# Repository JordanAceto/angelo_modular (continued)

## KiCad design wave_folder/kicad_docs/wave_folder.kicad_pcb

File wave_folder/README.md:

# Wavefolder

The wavefolder is a unique waveshaping circuit that creates "folded" versions of sloping input waveforms.

CV inputs for folds, shape, and offset are included.

A bonus ring-modulator circuit is included, to maintain compatability with the old module.

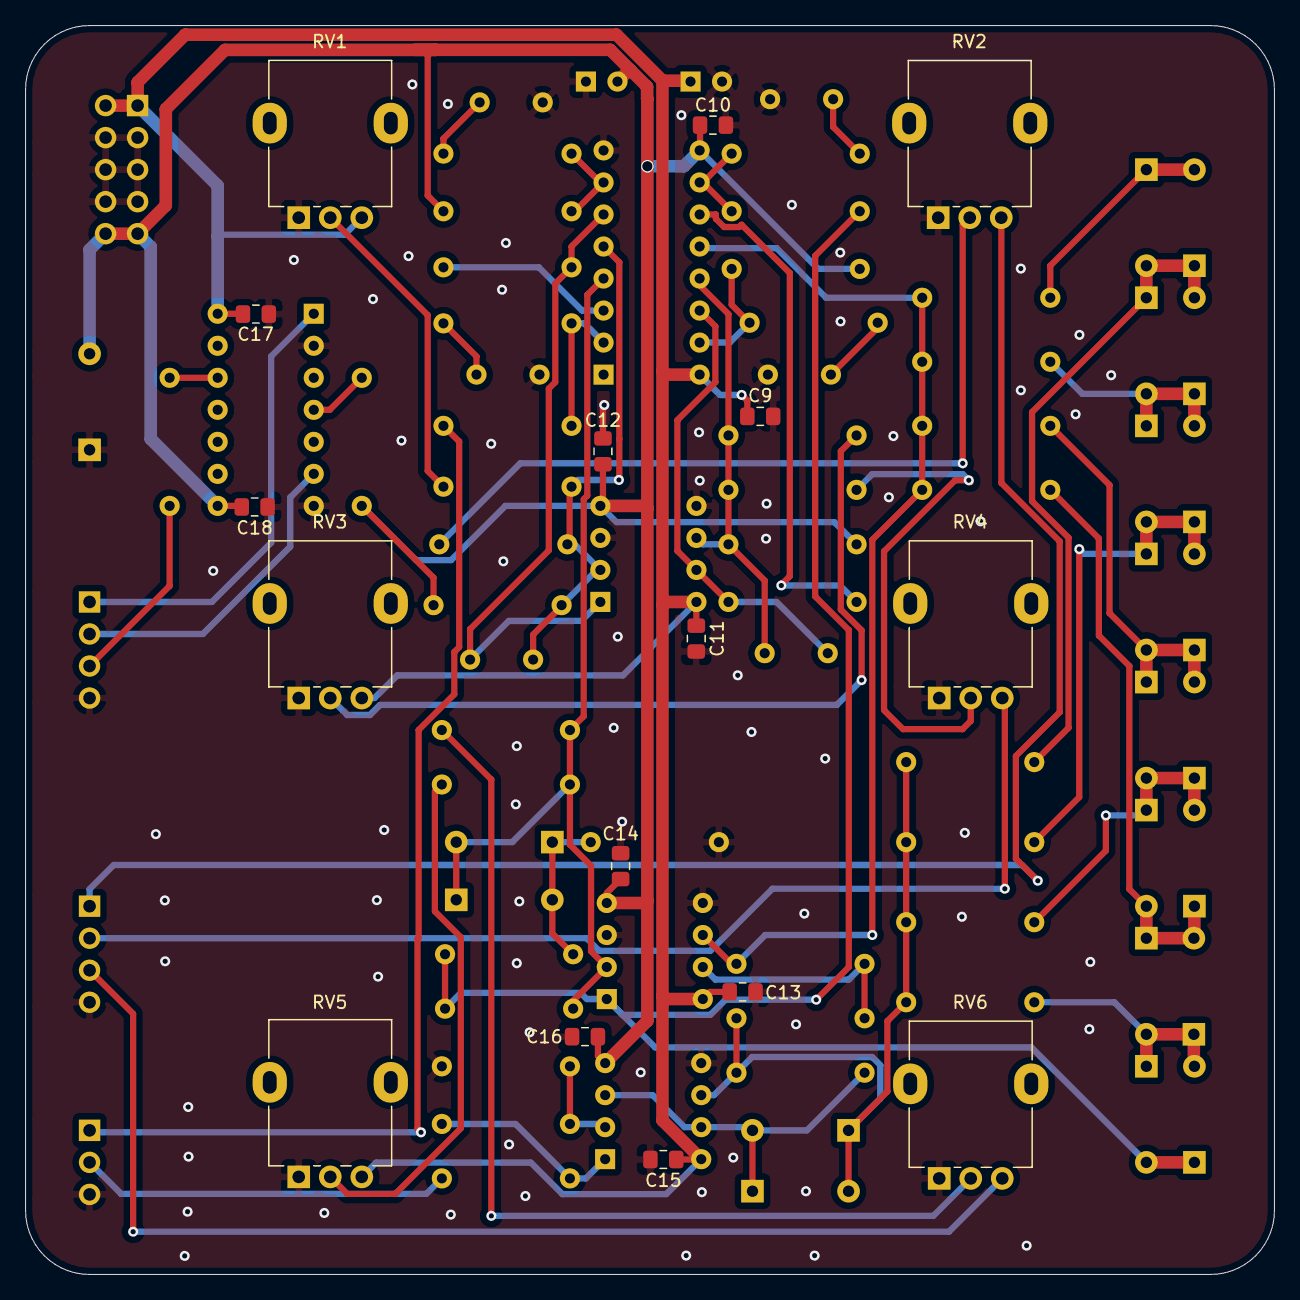
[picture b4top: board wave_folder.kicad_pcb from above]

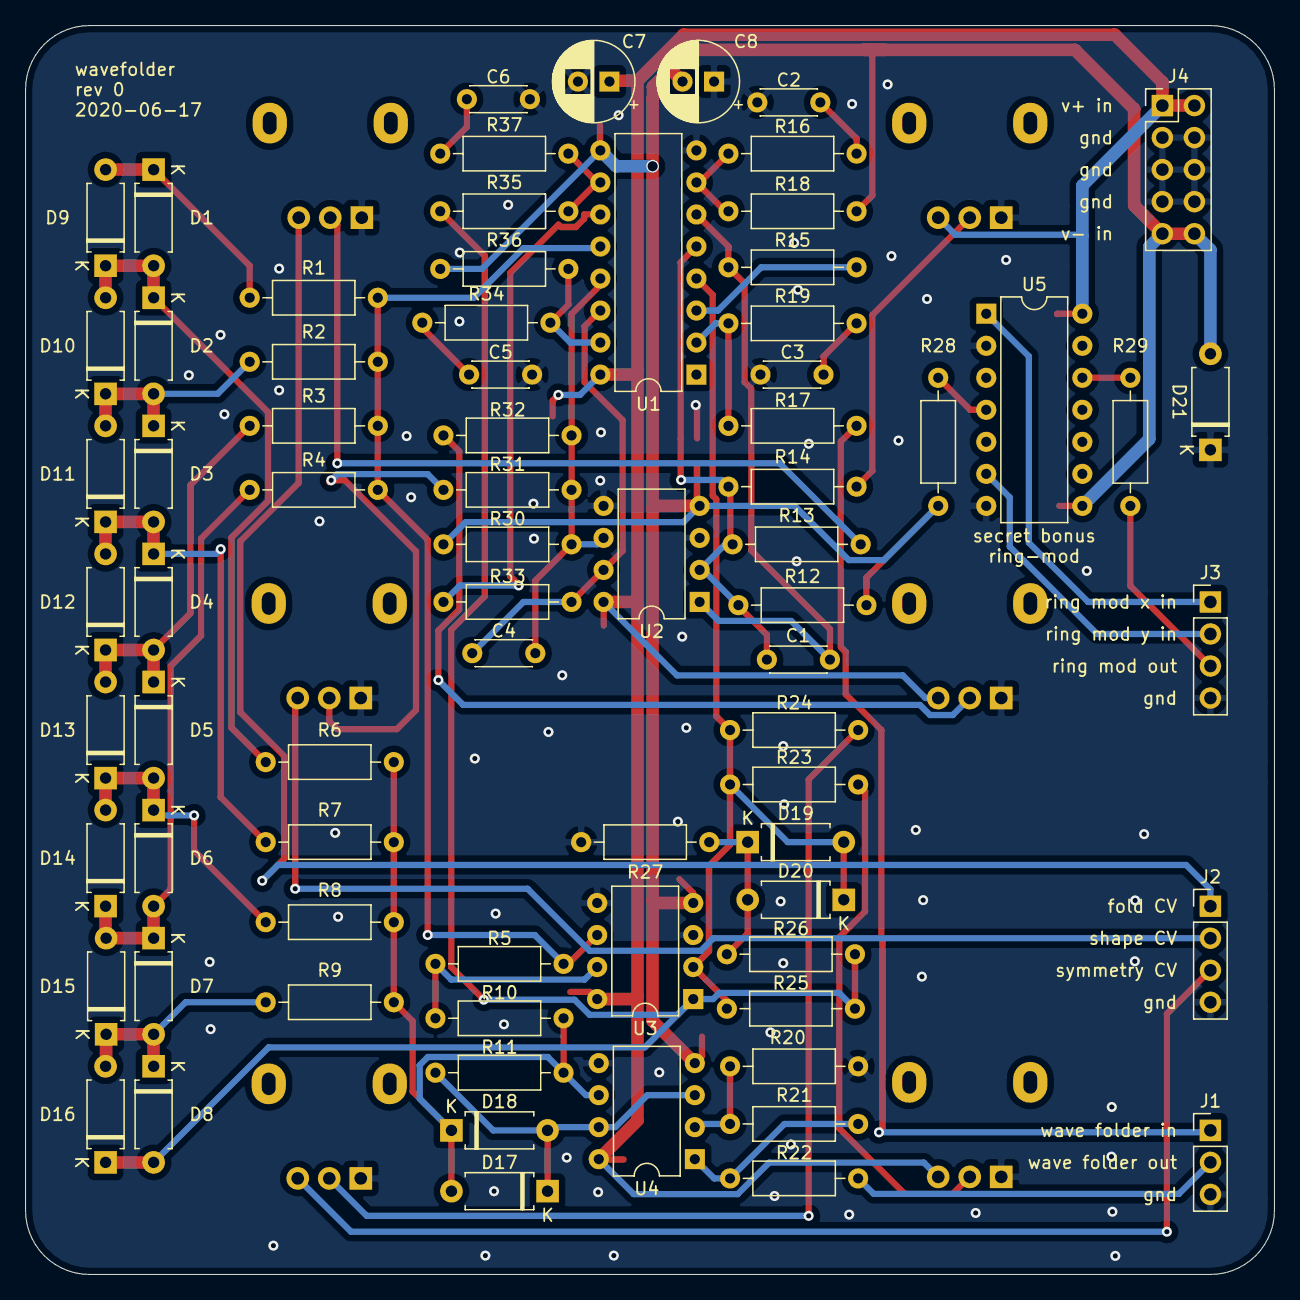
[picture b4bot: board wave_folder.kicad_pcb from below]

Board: 2 copper layers, 99.1 x 99.1 mm, 91 parts (75 on the bottom side), 50 nets.

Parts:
C1, C4: 100pF; C_Disc_D4.3mm_W1.9mm_P5.00mm
C2, C3, C5, C6: 560pF; C_Disc_D4.3mm_W1.9mm_P5.00mm
C7, C8: 10uF; CP_Radial_D6.3mm_P2.50mm
C9, C10, C11, C12, C13, C14, C15, C16, C17, C18: 100nF; C_0805_2012Metric_Pad1.15x1.40mm_HandSolder
D1, D2, D3, D4, D5, D6, D7, D8, D9, D10, D11, D12, D13, D14, D15, D16, D17, D18, D19, D20: D; D_A-405_P7.62mm_Horizontal
D21: D_Schottky; D_A-405_P7.62mm_Horizontal
J1: signal_port; PinHeader_1x03_P2.54mm_Vertical
J2: CV_port; PinHeader_1x04_P2.54mm_Vertical
J3: ring_mod_port; PinHeader_1x04_P2.54mm_Vertical
J4: power_in_connector; PinHeader_2x05_P2.54mm_Vertical
R1, R2, R3, R4, R6, R7, R8, R9: 15k; R_Axial_DIN0207_L6.3mm_D2.5mm_P10.16mm_Horizontal
R5, R10, R28: 5k6; R_Axial_DIN0207_L6.3mm_D2.5mm_P10.16mm_Horizontal
R11: 56k; R_Axial_DIN0207_L6.3mm_D2.5mm_P10.16mm_Horizontal
R12: dnf; R_Axial_DIN0207_L6.3mm_D2.5mm_P10.16mm_Horizontal
R13, R17, R24, R31: 100k; R_Axial_DIN0207_L6.3mm_D2.5mm_P10.16mm_Horizontal
R14, R23, R32: 220k; R_Axial_DIN0207_L6.3mm_D2.5mm_P10.16mm_Horizontal
R15, R33: 4k7; R_Axial_DIN0207_L6.3mm_D2.5mm_P10.16mm_Horizontal
R16, R19, R34, R37: 510; R_Axial_DIN0207_L6.3mm_D2.5mm_P10.16mm_Horizontal
R18, R36: 240k; R_Axial_DIN0207_L6.3mm_D2.5mm_P10.16mm_Horizontal
R20: 7k5; R_Axial_DIN0207_L6.3mm_D2.5mm_P10.16mm_Horizontal
R21: 82k; R_Axial_DIN0207_L6.3mm_D2.5mm_P10.16mm_Horizontal
R22, R29: 1k; R_Axial_DIN0207_L6.3mm_D2.5mm_P10.16mm_Horizontal
R25: 180k; R_Axial_DIN0207_L6.3mm_D2.5mm_P10.16mm_Horizontal
R26: 33k; R_Axial_DIN0207_L6.3mm_D2.5mm_P10.16mm_Horizontal
R27: 2k7; R_Axial_DIN0207_L6.3mm_D2.5mm_P10.16mm_Horizontal
R30: 10M; R_Axial_DIN0207_L6.3mm_D2.5mm_P10.16mm_Horizontal
R35: 27k; R_Axial_DIN0207_L6.3mm_D2.5mm_P10.16mm_Horizontal
RV1, RV2, RV3, RV4, RV5, RV6: 100k; Potentiometer_Alpha_RD901F-40-00D_Single_Vertical
U1: SSM2164; DIP-16_W7.62mm
U2, U3, U4: TL072; DIP-8_W7.62mm
U5: AD534; DIP-14_W7.62mm

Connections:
+12V: C7.1, C9.1, C11.1, C13.1, C15.1, C17.1, J4.1, J4.2, RV1.3, RV3.3, RV5.3, U1.16, U2.8, U3.8, U4.8, U5.14
-12V: C8.2, C10.2, C12.2, C14.2, C16.2, C18.2, D21.2, J4.9, J4.10, R12.2, R18.1, R28.2, R30.2, R36.1, U1.9, U2.4, U3.4, U4.4, U5.8
/core/core_i_in: R1.2, R2.2, R3.2, R4.2, R5.2, U1.12, U3.6
/core/core_out: D17.1, D18.2, R11.1, U4.3, U4.7
/core/core_v_in: D8.2, D16.1, R25.1, R26.1, R35.2, U3.1
/folds_CV: R13.2, RV2.2
/folds_CV_in: J2.1, RV2.3
/folds_VCA/folds_VCA_signal_i_out: D19.2, D20.1, R23.1, R24.1, R25.2, U1.4, U3.2
/manual_folds: R14.2, RV1.2
/manual_shape: R32.2, RV3.2
/manual_symmetry: R23.2, RV5.2
/ring_mod_out: J3.3, R29.1
/ring_mod_x_in: J3.1, U5.1
/ring_mod_y_in: J3.2, U5.6
/shape_CV: R31.2, RV4.2
/shape_CV_in: J2.2, RV4.3
/signal_in: J1.1, R17.2
/signal_out: J1.2, R22.2
/symmetry_CV: R24.2, RV6.2
/symmetry_CV_in: J2.3, RV6.3
GND: C2.2, C3.2, C5.2, C6.2, C7.2, C8.1, C9.2, C10.1, C11.2, C12.1, C13.2, C14.1, C15.2, C16.1, C17.2, C18.1, D21.1, J1.3, J2.4, J3.4, J4.3, J4.4, J4.5, J4.6, J4.7, J4.8, R20.1, R27.2, RV1.1, RV2.1, RV3.1, RV4.1, RV5.1, RV6.1, U1.8, U2.3, U2.5, U3.3, U3.5, U4.5, U5.2, U5.7
unnamed: C1.1, R15.2, U1.6, U2.1
unnamed: C1.2, R12.1, R13.1, R14.1, U1.5, U2.2
unnamed: C2.1, R16.1
unnamed: C3.1, R19.1
unnamed: C4.1, R33.2, U1.14, U2.7
unnamed: C4.2, R30.1, R31.1, R32.1, U1.13, U2.6
unnamed: C5.1, R34.1
unnamed: C6.1, R37.1
unnamed: D1.1, D9.2, R1.1
unnamed: D1.2, D2.1, D9.1, D10.2, R6.2
unnamed: D2.2, D3.1, D10.1, D11.2, R2.1
unnamed: D3.2, D4.1, D11.1, D12.2, R7.2
unnamed: D4.2, D5.1, D12.1, D13.2, R3.1
unnamed: D5.2, D6.1, D13.1, D14.2, R8.2
unnamed: D6.2, D7.1, D14.1, D15.2, R4.1
unnamed: D7.2, D8.1, D15.1, D16.2, R9.2
unnamed: D17.2, D18.1, R6.1, R7.1, R8.1, R9.1, R10.1, R11.2, U4.6
unnamed: D19.1, D20.2, R26.2, R27.1
unnamed: R5.1, R10.2, U3.7
unnamed: R15.1, U1.3
unnamed: R16.2, R18.2, U1.7
unnamed: R17.1, R19.2, U1.2
unnamed: R20.2, R21.1, U4.2
unnamed: R21.2, R22.1, U4.1
unnamed: R28.1, U5.4
unnamed: R29.2, U5.12
unnamed: R33.1, U1.11
unnamed: R34.2, R36.2, U1.15
unnamed: R35.1, R37.2, U1.10

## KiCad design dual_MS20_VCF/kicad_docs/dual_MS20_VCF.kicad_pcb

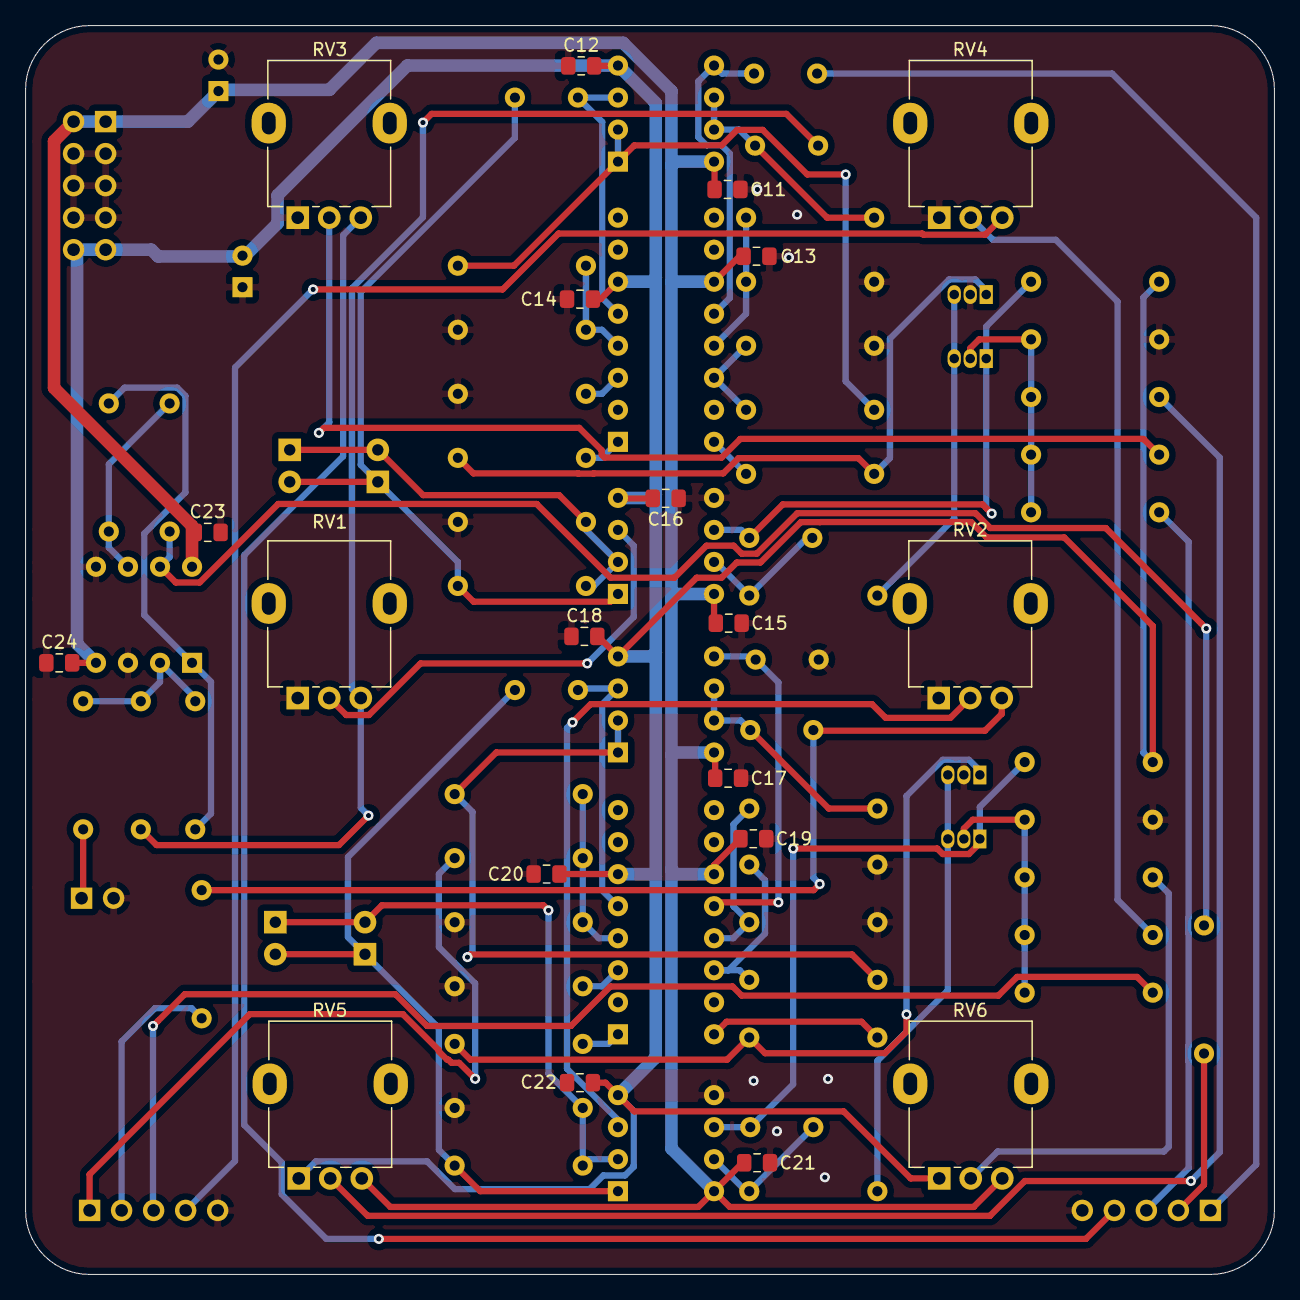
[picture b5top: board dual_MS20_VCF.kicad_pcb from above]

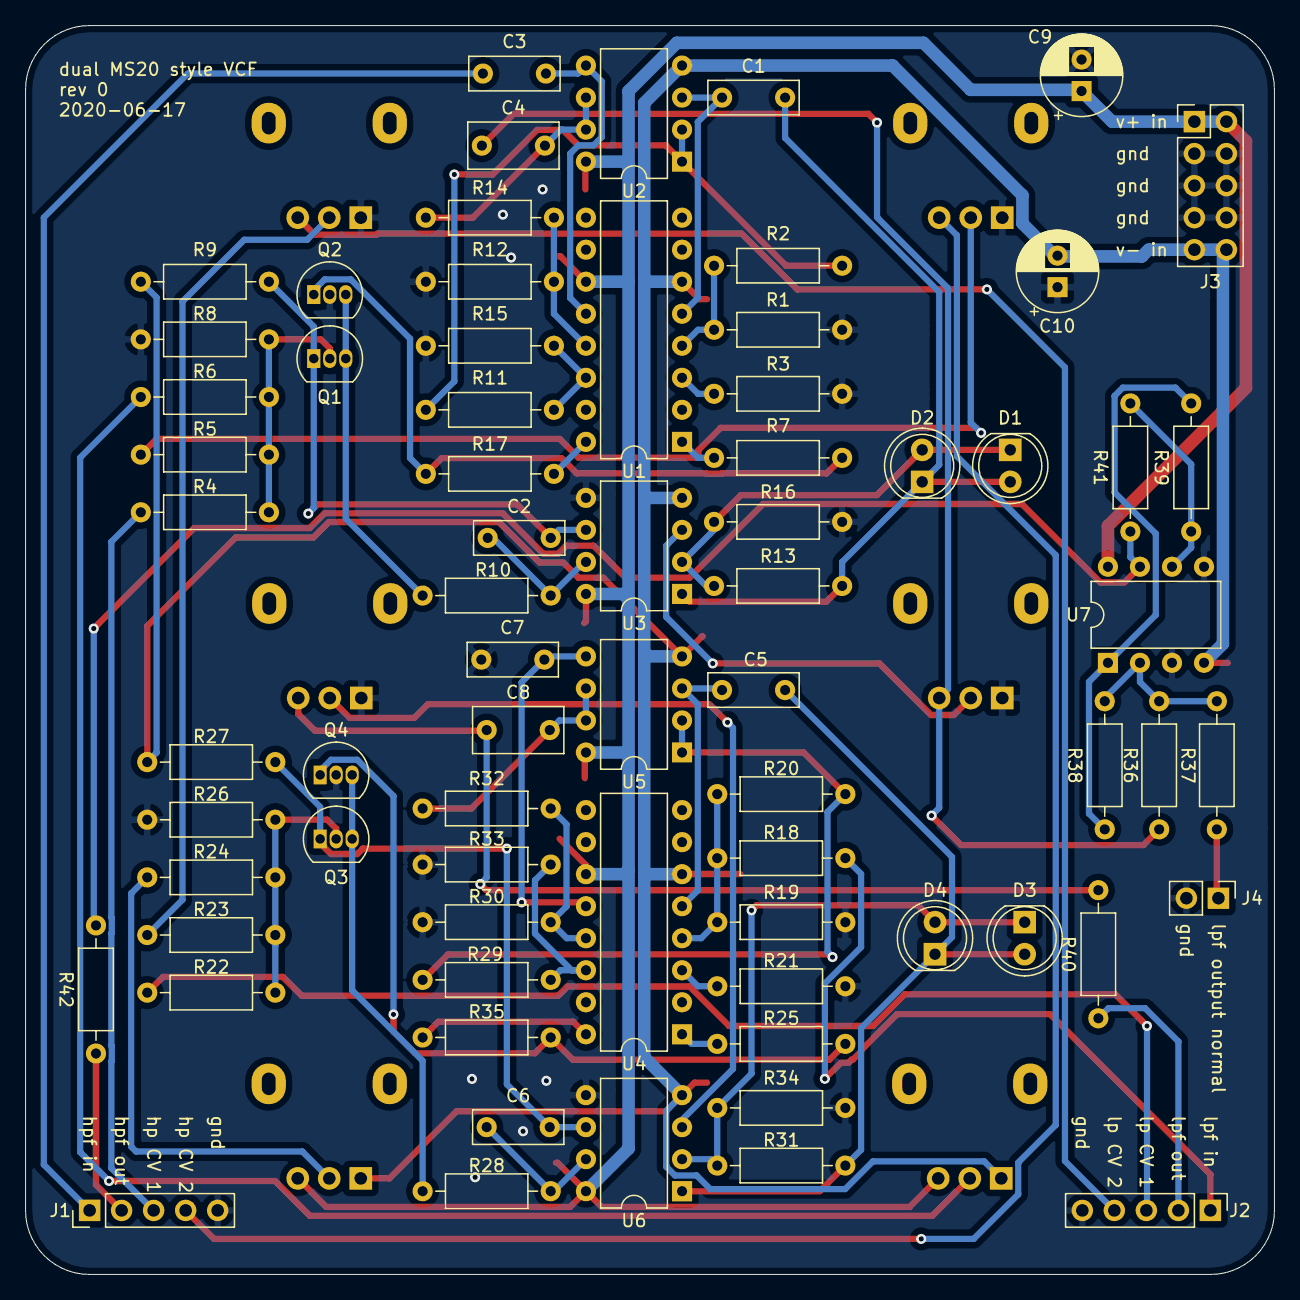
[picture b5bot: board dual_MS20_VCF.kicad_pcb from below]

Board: 2 copper layers, 99.1 x 99.1 mm, 91 parts (71 on the bottom side), 58 nets.

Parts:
C1, C3, C5, C7: 1nF; C_Rect_L7.0mm_W2.5mm_P5.00mm
C2, C6: 4n7; C_Rect_L7.0mm_W2.5mm_P5.00mm
C4, C8: 470nF; C_Rect_L7.0mm_W3.5mm_P5.00mm
C9, C10: 10uF; CP_Radial_D6.3mm_P2.50mm
C11, C12, C13, C14, C15, C16, C17, C18, C19, C20, C21, C22, C23, C24: 100nF; C_0805_2012Metric_Pad1.15x1.40mm_HandSolder
D1, D2, D3, D4: green; LED_D5.0mm
J1, J2: Conn_01x05; PinHeader_1x05_P2.54mm_Vertical
J3: power_in; PinHeader_2x05_P2.54mm_Vertical
J4: lpf_output_normal; PinHeader_1x02_P2.54mm_Vertical
Q1, Q2, Q3, Q4: BC558; TO-92_Inline
R1, R3, R12, R15, R19, R21, R30, R33: 220; R_Axial_DIN0207_L6.3mm_D2.5mm_P10.16mm_Horizontal
R2, R7, R11, R13, R14, R17, R18, R20, R25, R29, R31, R32, R35: 10k; R_Axial_DIN0207_L6.3mm_D2.5mm_P10.16mm_Horizontal
R4, R5, R22, R23, R36, R37, R38, R39, R41: 100k; R_Axial_DIN0207_L6.3mm_D2.5mm_P10.16mm_Horizontal
R6, R24: 240k; R_Axial_DIN0207_L6.3mm_D2.5mm_P10.16mm_Horizontal
R8, R16, R26, R34: 1k8; R_Axial_DIN0207_L6.3mm_D2.5mm_P10.16mm_Horizontal
R9, R27: 470k; R_Axial_DIN0207_L6.3mm_D2.5mm_P10.16mm_Horizontal
R10, R28: 4k7; R_Axial_DIN0207_L6.3mm_D2.5mm_P10.16mm_Horizontal
R40, R42: 1k; R_Axial_DIN0207_L6.3mm_D2.5mm_P10.16mm_Horizontal
RV1, RV2, RV3, RV4, RV5, RV6: 100k; Potentiometer_Alpha_RD901F-40-00D_Single_Vertical
U1, U4: LM13700; DIP-16_W7.62mm
U2, U3, U5, U6: MC1458; DIP-8_W7.62mm
U7: TL072; DIP-8_W7.62mm

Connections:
+12V: C9.1, C11.1, C13.1, C15.1, C17.1, C19.1, C21.1, C23.1, J3.1, J3.2, RV5.3, RV6.3, U1.11, U2.8, U3.8, U4.11, U5.8, U6.8, U7.8
-12V: C10.2, C12.2, C14.2, C16.2, C18.2, C20.2, C22.2, C24.2, J3.9, J3.10, R9.2, R27.2, RV5.1, RV6.1, U1.6, U2.4, U3.4, U4.6, U5.4, U6.4, U7.4
/HPF/hpf_cv_in_1: J1.3, R4.2
/HPF/hpf_cv_in_2: R5.2, RV3.2
/HPF/hpf_cv_in_3: R6.2, RV5.2
/HPF/hpf_in: C3.2, J1.1
/HPF/i_out: Q2.1, R7.1, R17.1
/LPF/i_out: Q4.1, R25.1, R35.1
/LPF/lpf_cv_in_1: J2.3, R22.2
/LPF/lpf_cv_in_2: R23.2, RV4.2
/LPF/lpf_cv_in_3: R24.2, RV6.2
/LPF/lpf_in: J2.1, R18.2
/LPF/lpf_out: C8.1, R40.2, RV2.3
/high_pass: C4.1, R36.2, RV1.3
/low_pass: J2.2, R40.1
/summed_hp_lp: J1.2, R42.1
GND: C7.2, C9.2, C10.1, C11.2, C12.1, C13.2, C14.1, C15.2, C16.1, C17.2, C18.1, C19.2, C20.1, C21.2, C22.1, C23.2, C24.1, J1.5, J2.5, J3.3, J3.4, J3.5, J3.6, J3.7, J3.8, J4.2, Q2.2, Q4.2, R1.2, R3.2, R8.2, R12.2, R15.2, R16.2, R19.2, R21.2, R26.2, R30.2, R33.2, R34.2, RV1.1, RV2.1, RV3.1, RV4.1, U3.5, U6.5, U7.3, U7.5
unnamed: C1.1, U1.5, U2.3
unnamed: C1.2, D1.2, D2.1, R13.2, U3.1
unnamed: C2.1, R10.1, U3.7
unnamed: C2.2, Q1.1, R9.1, U3.6
unnamed: C3.1, U1.12, U2.5
unnamed: C4.2, R14.1, U2.6, U2.7
unnamed: C5.1, U4.5, U5.3
unnamed: C5.2, D3.2, D4.1, R31.2, U6.1
unnamed: C6.1, R28.1, U6.7
unnamed: C6.2, Q3.1, R27.1, U6.6
unnamed: C7.1, U4.12, U5.5
unnamed: C8.2, R32.1, U5.6, U5.7
unnamed: D1.1, D2.2, R13.1, R16.1, U3.2
unnamed: D3.1, D4.2, R31.1, R34.1, U6.2
unnamed: J1.4, RV3.3
unnamed: J2.4, RV4.3
unnamed: J4.1, R37.2
unnamed: Q1.2, R4.1, R5.1, R6.1, R8.1
unnamed: Q1.3, Q2.3, R10.2
unnamed: Q3.2, R22.1, R23.1, R24.1, R26.1
unnamed: Q3.3, Q4.3, R28.2
unnamed: R1.1, R2.2, U1.4
unnamed: R3.1, U1.3
unnamed: R7.2, U1.1
unnamed: R11.1, R15.1, U1.14
unnamed: R2.1, R11.2, U2.1, U2.2
unnamed: R12.1, R14.2, U1.13
unnamed: R17.2, U1.16
unnamed: R18.1, R19.1, R20.2, U4.4
unnamed: R20.1, R29.2, U5.1, U5.2
unnamed: R21.1, U4.3
unnamed: R25.2, U4.1
unnamed: R29.1, R33.1, U4.14
unnamed: R30.1, R32.2, U4.13
unnamed: R35.2, U4.16
unnamed: R36.1, R37.1, R38.2, U7.2
unnamed: R38.1, R39.2, U7.1
unnamed: R39.1, R41.2, U7.6
unnamed: R41.1, R42.2, U7.7
unnamed: RV1.2, U3.3
unnamed: RV2.2, U6.3

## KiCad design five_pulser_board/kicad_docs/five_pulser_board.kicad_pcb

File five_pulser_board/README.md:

# 5-Pulser auxilliary waveshaper board

Small aux waveshaper pcb intended to be used with the oscillator carrier boards.

The 5-pulser is a unique pulse shaper that takes in sloping wave inputs and outputs a stream of between 1 and 5 pulses. The typical input is sawtooth waves.

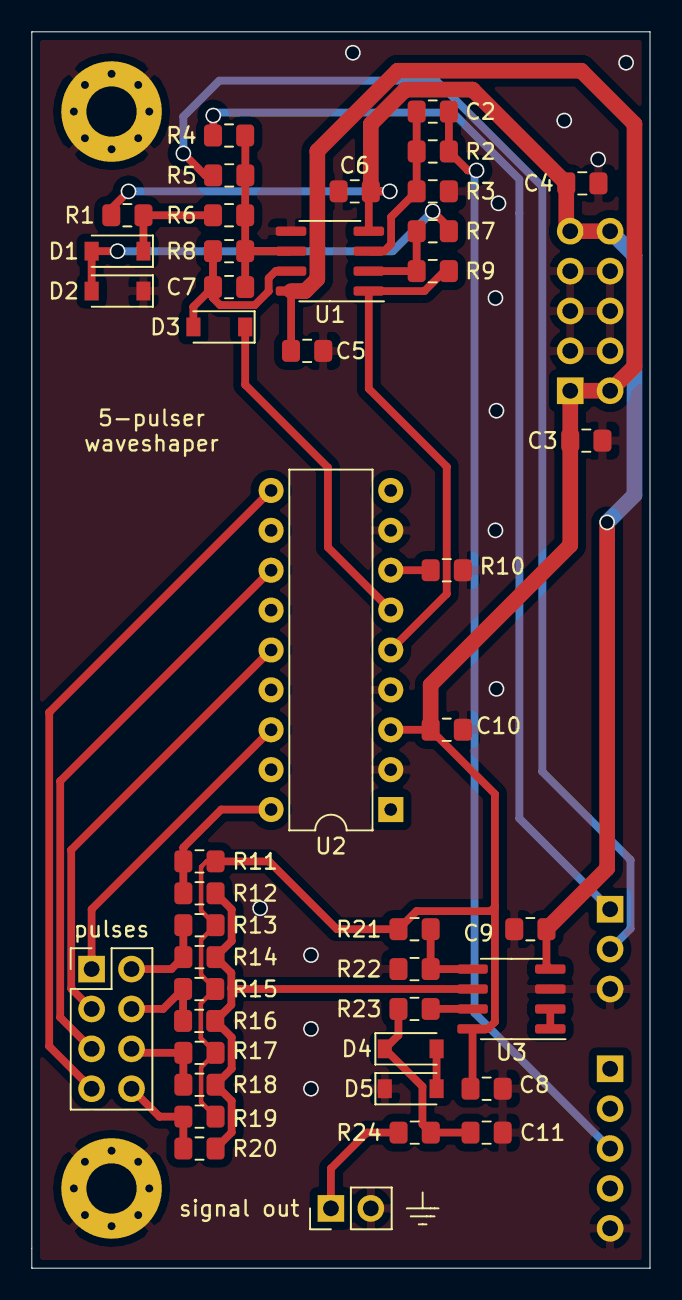
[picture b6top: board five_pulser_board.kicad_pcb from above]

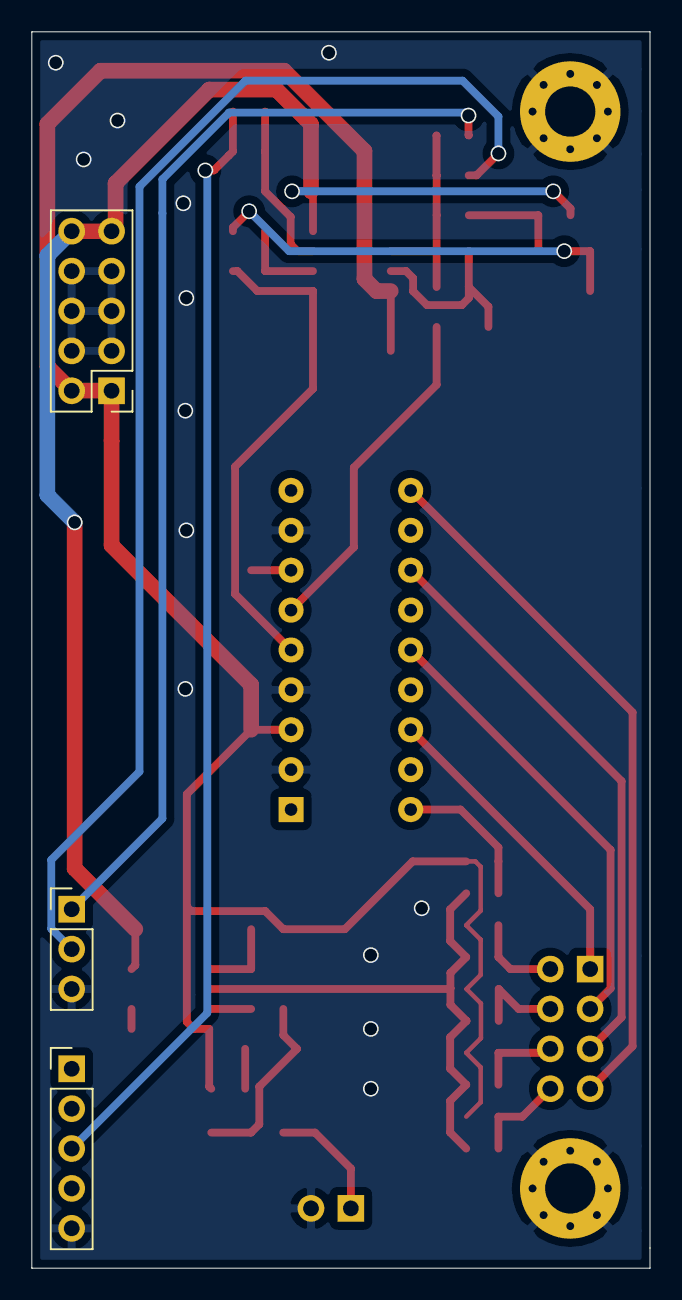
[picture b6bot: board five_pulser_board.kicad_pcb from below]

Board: 2 copper layers, 39.4 x 78.7 mm, 49 parts (3 on the bottom side), 31 nets.

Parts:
C2: 10pF; C_0805_2012Metric_Pad1.15x1.40mm_HandSolder
C3, C4: 10uF; C_0805_2012Metric_Pad1.15x1.40mm_HandSolder
C5, C6, C7, C8, C9, C10: 100nF; C_0805_2012Metric_Pad1.15x1.40mm_HandSolder
C11: 10nF; C_0805_2012Metric_Pad1.15x1.40mm_HandSolder
D1, D3: 1N4148W; D_SOD-123
D2, D4, D5: 5v1; D_SOD-123
H1, H2: MountingHole_Pad; MountingHole_3.2mm_M3_Pad_Via
J1: signal_in; PinHeader_1x05_P2.54mm_Vertical
J2: CV_in; PinHeader_1x03_P2.54mm_Vertical
J3: Conn_02x05_Odd_Even; PinHeader_2x05_P2.54mm_Vertical
J4: signal_out; PinHeader_1x02_P2.54mm_Vertical
J5: pulses; PinHeader_2x04_P2.54mm_Vertical
R1, R21, R23: 3k9; R_0805_2012Metric_Pad1.15x1.40mm_HandSolder
R2, R5, R6, R7: 100k; R_0805_2012Metric_Pad1.15x1.40mm_HandSolder
R3, R9, R11, R13, R15, R17, R19: 10k; R_0805_2012Metric_Pad1.15x1.40mm_HandSolder
R4, R12: 120k; R_0805_2012Metric_Pad1.15x1.40mm_HandSolder
R8: 39k; R_0805_2012Metric_Pad1.15x1.40mm_HandSolder
R10: 5k6; R_0805_2012Metric_Pad1.15x1.40mm_HandSolder
R14, R16, R18, R20: 150k; R_0805_2012Metric_Pad1.15x1.40mm_HandSolder
R22: 22k; R_0805_2012Metric_Pad1.15x1.40mm_HandSolder
R24: 1k; R_0805_2012Metric_Pad1.15x1.40mm_HandSolder
U1, U3: TL072; SOIC-8_3.9x4.9mm_P1.27mm
U2: LM3914; DIP-18_W7.62mm

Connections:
+12V: C3.1, C5.1, C8.1, C10.1, J3.1, J3.2, R11.2, R13.2, R15.2, R17.2, R19.2, R21.2, U1.8, U2.3, U3.8
-5_volts: D1.2, D2.2, R7.2
-12V: C4.2, C6.2, C9.2, J3.9, J3.10, R1.2, U1.4, U3.4
GND: C3.2, C4.1, C5.2, C6.1, C8.2, C9.1, C10.2, C11.2, D2.1, D5.1, H1.1, H2.1, J1.5, J2.3, J3.3, J3.4, J3.5, J3.6, J3.7, J3.8, J4.2, R3.1, R10.2, R22.1, U1.5, U2.2, U2.4, U2.8, U3.3
unnamed: C2.1, R2.2, R3.2, U1.3
unnamed: C2.2, J1.3, R2.1
unnamed: C7.1, D3.2, R8.1, U1.7
unnamed: C7.2, R4.1, R5.1, R6.1, R8.2, U1.6
unnamed: C11.1, D4.1, R23.1, R24.2
unnamed: D1.1, R1.1, R6.2
unnamed: D3.1, U2.6
unnamed: D4.2, D5.2
unnamed: J2.1, R4.2
unnamed: J2.2, R5.2
unnamed: J4.1, R24.1
unnamed: J5.1, U2.16
unnamed: J5.2, R13.1, R14.2
unnamed: J5.3, U2.14
unnamed: J5.4, R15.1, R16.2
unnamed: J5.5, U2.12
unnamed: J5.6, R17.1, R18.2
unnamed: J5.7, U2.10
unnamed: J5.8, R19.1, R20.2
unnamed: R7.1, R9.2, U1.2
unnamed: R9.1, U1.1, U2.5
unnamed: R10.1, U2.7
unnamed: R11.1, R12.2, U2.18
unnamed: R12.1, R14.1, R16.1, R18.1, R20.1, U3.6
unnamed: R21.1, R22.2, U3.5
unnamed: R23.2, U3.7
unnamed: U3.1, U3.2

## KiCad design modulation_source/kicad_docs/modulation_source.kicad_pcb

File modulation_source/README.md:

# Modulation Source

PCB with a voltage controlled LFO, sample-and-hold, and white noise source.

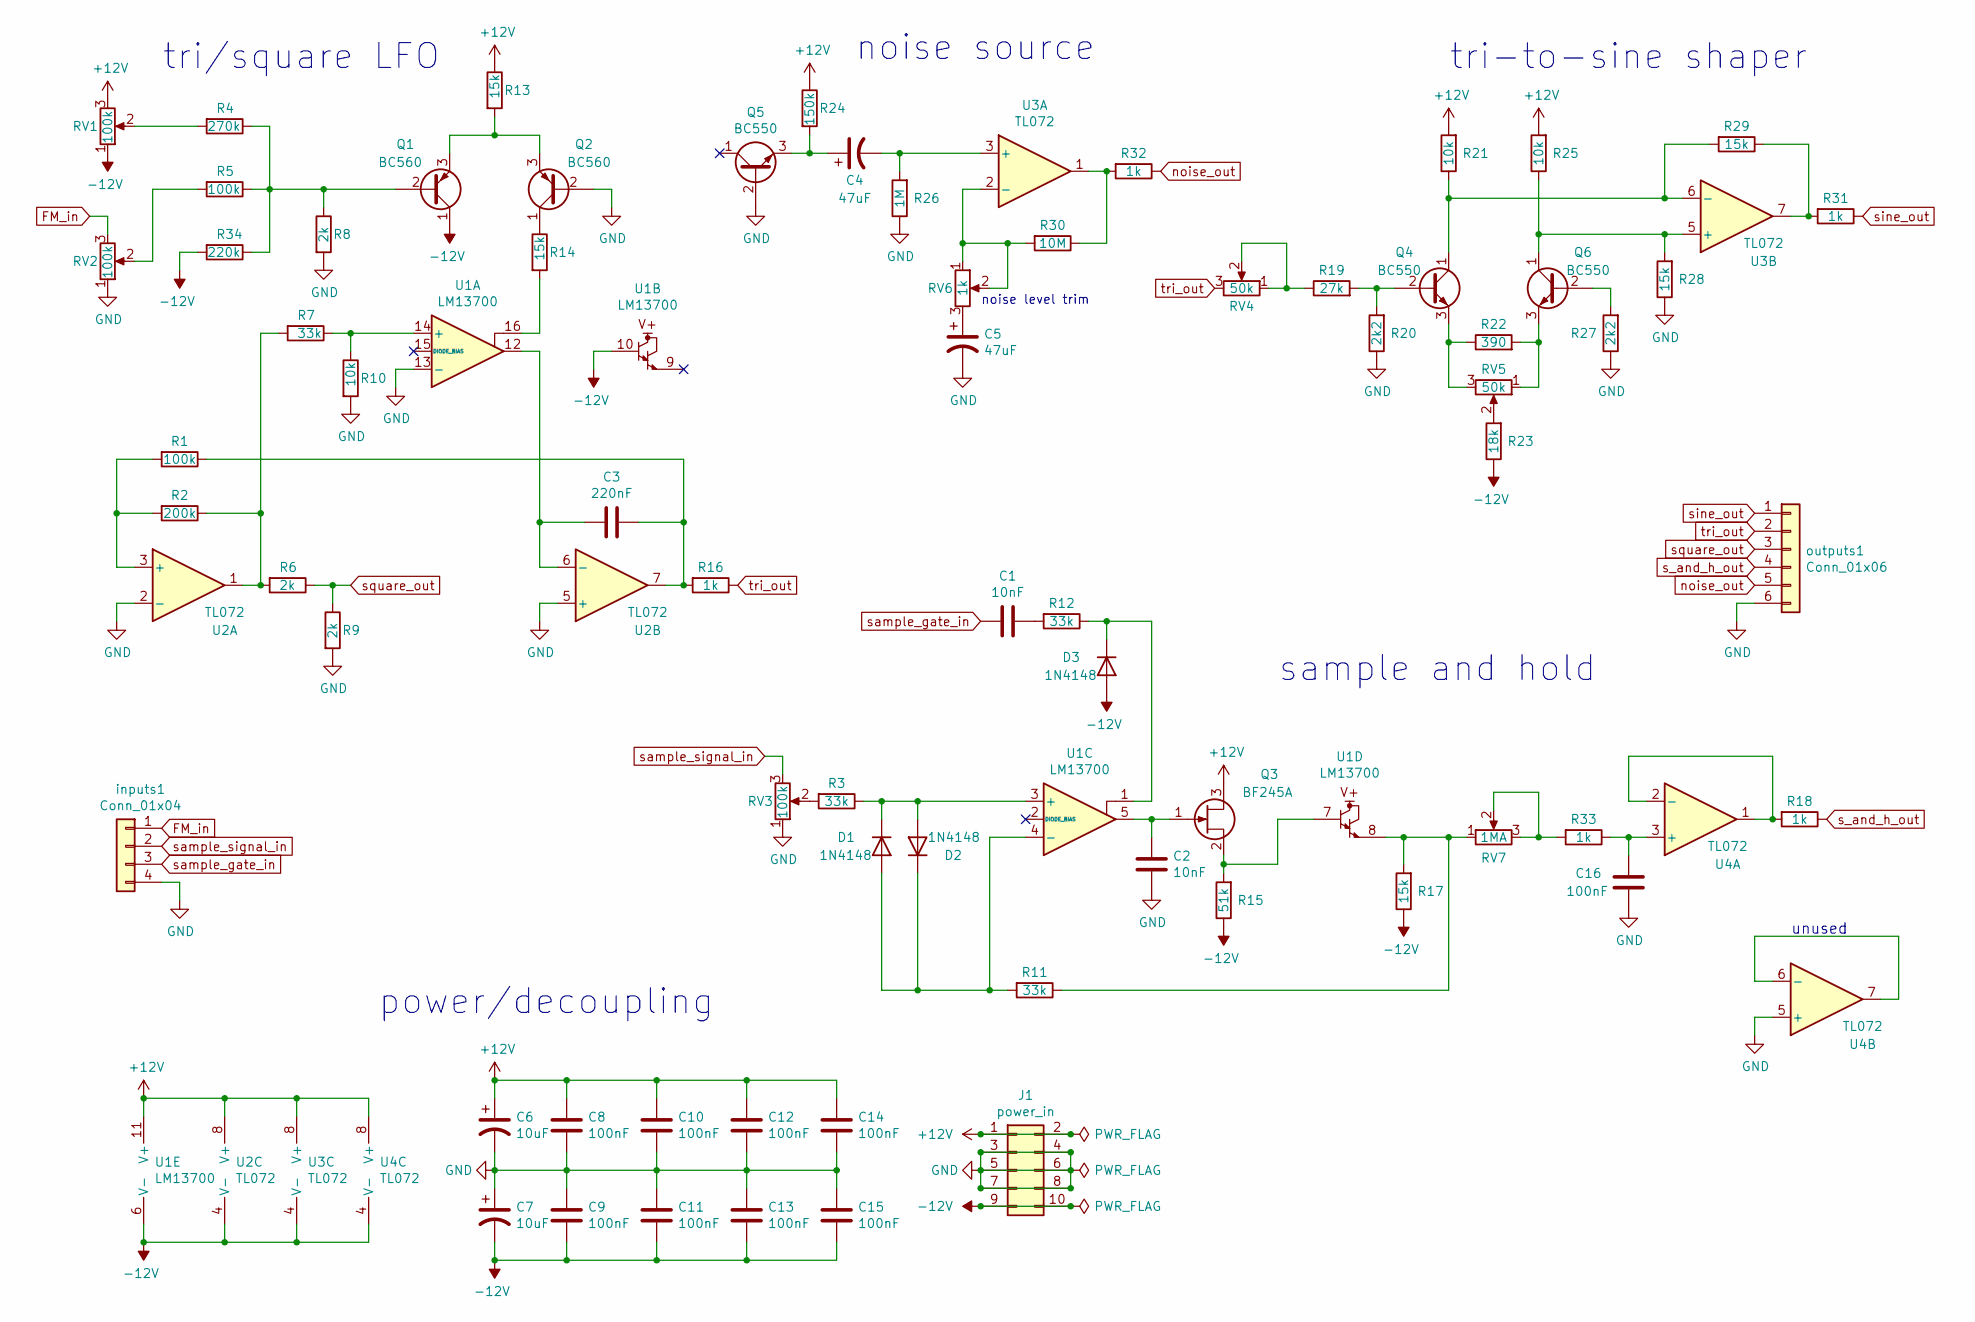
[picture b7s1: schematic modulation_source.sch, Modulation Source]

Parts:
C1, C2: 10nF; C_0805_2012Metric_Pad1.15x1.40mm_HandSolder
C3: 220nF; C_0805_2012Metric_Pad1.15x1.40mm_HandSolder
C4, C5: 47uF; CP_Radial_D6.3mm_P2.50mm
C6, C7: 10uF; CP_Radial_D6.3mm_P2.50mm
C8, C9, C10, C11, C12, C13, C14, C15, C16: 100nF; C_0805_2012Metric_Pad1.15x1.40mm_HandSolder
D1, D2, D3: 1N4148; D_DO-35_SOD27_P7.62mm_Horizontal
J1: power_in; PinHeader_2x05_P2.54mm_Vertical
Q1, Q2: BC560; TO-92_Inline
Q3: BF245A; TO-92_Inline
Q4, Q5, Q6: BC550; TO-92_Inline
R1, R5: 100k; R_0805_2012Metric_Pad1.15x1.40mm_HandSolder
R2: 200k; R_0805_2012Metric_Pad1.15x1.40mm_HandSolder
R3, R7, R11, R12: 33k; R_0805_2012Metric_Pad1.15x1.40mm_HandSolder
R4: 270k; R_0805_2012Metric_Pad1.15x1.40mm_HandSolder
R6, R8, R9: 2k; R_0805_2012Metric_Pad1.15x1.40mm_HandSolder
R10, R21, R25: 10k; R_0805_2012Metric_Pad1.15x1.40mm_HandSolder
R13, R14, R17, R28, R29: 15k; R_0805_2012Metric_Pad1.15x1.40mm_HandSolder
R15: 51k; R_0805_2012Metric_Pad1.15x1.40mm_HandSolder
R16, R18, R31, R32, R33: 1k; R_0805_2012Metric_Pad1.15x1.40mm_HandSolder
R19: 27k; R_0805_2012Metric_Pad1.15x1.40mm_HandSolder
R20, R27: 2k2; R_0805_2012Metric_Pad1.15x1.40mm_HandSolder
R22: 390; R_0805_2012Metric_Pad1.15x1.40mm_HandSolder
R23: 18k; R_0805_2012Metric_Pad1.15x1.40mm_HandSolder
R24: 150k; R_0805_2012Metric_Pad1.15x1.40mm_HandSolder
R26: 1M; R_0805_2012Metric_Pad1.15x1.40mm_HandSolder
R30: 10M; R_0805_2012Metric_Pad1.15x1.40mm_HandSolder
R34: 220k; R_0805_2012Metric_Pad1.15x1.40mm_HandSolder
RV1, RV2, RV3: 100k; Potentiometer_Alpha_RD901F-40-00D_Single_Vertical
RV4, RV5: 50k; Potentiometer_Bourns_3296W_Vertical
RV6: 1k; Potentiometer_Bourns_3296W_Vertical
RV7: 1MA; Potentiometer_Alpha_RD901F-40-00D_Single_Vertical
U1: LM13700; DIP-16_W7.62mm
U2, U3, U4: TL072; DIP-8_W7.62mm
inputs1: Conn_01x04; PinHeader_1x04_P2.54mm_Vertical
outputs1: Conn_01x06; PinHeader_1x06_P2.54mm_Vertical

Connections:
+12V: C6.1, C8.1, C10.1, C12.1, C14.1, J1.1, J1.2, Q3.3 (D), R13.1, R21.2, R24.1, R25.2, RV1.3, U1.11 (V+), U2.8 (V+), U3.8 (V+), U4.8 (V+)
-12V: C7.2, C9.2, C11.2, C13.2, C15.2, D3.2 (A), J1.9, J1.10, Q1.1 (C), R15.1, R17.1, R23.1, R34.2, RV1.1, U1.6 (V-), U1.10, U2.4 (V-), U3.4 (V-), U4.4 (V-)
FM_in: RV2.3, inputs1.1
GND: C2.1, C5.2, C6.2, C7.1, C8.2, C9.1, C10.2, C11.1, C12.2, C13.1, C14.2, C15.1, C16.2, J1.3, J1.4, J1.5, J1.6, J1.7, J1.8, Q2.2 (B), Q5.2 (B), R8.2, R9.2, R10.2, R20.1, R26.1, R27.1, R28.1, RV2.1, RV3.1, U1.13 (-), U2.2 (-), U2.5 (+), U4.5 (+), inputs1.4, outputs1.6
unnamed: C1.1, R12.2
unnamed: C2.2, Q3.1 (G), U1.5
unnamed: C3.1, R1.1, R16.2, U2.7
unnamed: C3.2, U1.12, U2.6 (-)
unnamed: C4.1, Q5.3 (E), R24.2
unnamed: C4.2, R26.2, U3.3 (+)
unnamed: C5.1, RV6.3
unnamed: C16.1, R33.1, U4.3 (+)
unnamed: D1.1 (K), D2.2 (A), R3.1, U1.3 (+)
unnamed: D1.2 (A), D2.1 (K), R11.2, U1.4 (-)
unnamed: D3.1 (K), R12.1, U1.1
unnamed: Q1.2 (B), R4.1, R5.1, R8.1, R34.1
unnamed: Q1.3 (E), Q2.3 (E), R13.2
unnamed: Q2.1 (C), R14.1
unnamed: Q3.2 (S), R15.2, U1.7
unnamed: Q4.1 (C), R21.1, R29.2, U3.6 (-)
unnamed: Q4.2 (B), R19.2, R20.2
unnamed: Q4.3 (E), R22.1, RV5.3
unnamed: Q6.1 (C), R25.1, R28.2, U3.5 (+)
unnamed: Q6.2 (B), R27.2
unnamed: Q6.3 (E), R22.2, RV5.1
unnamed: R1.2, R2.2, U2.3 (+)
unnamed: R2.1, R6.2, R7.2, U2.1
unnamed: R3.2, RV3.2
unnamed: R4.2, RV1.2
unnamed: R5.2, RV2.2
unnamed: R7.1, R10.1, U1.14 (+)
unnamed: R11.1, R17.2, RV7.1, U1.8
unnamed: R14.2, U1.16
unnamed: R18.2, U4.1, U4.2 (-)
unnamed: R19.1, RV4.1, RV4.2
unnamed: R23.2, RV5.2
unnamed: R29.1, R31.2, U3.7
unnamed: R30.1, R32.2, U3.1
unnamed: R30.2, RV6.1, RV6.2, U3.2 (-)
unnamed: R33.2, RV7.2, RV7.3
unnamed: U4.6 (-), U4.7
noise_out: R32.1, outputs1.5
s_and_h_out: R18.1, outputs1.4
sample_gate_in: C1.2, inputs1.3
sample_signal_in: RV3.3, inputs1.2
sine_out: R31.1, outputs1.1
square_out: R6.1, R9.1, outputs1.3
tri_out: R16.1, RV4.3, outputs1.2

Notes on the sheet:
noise level trim
tri/square LFO
noise source
tri-to-sine shaper
sample and hold
unused
power/decoupling

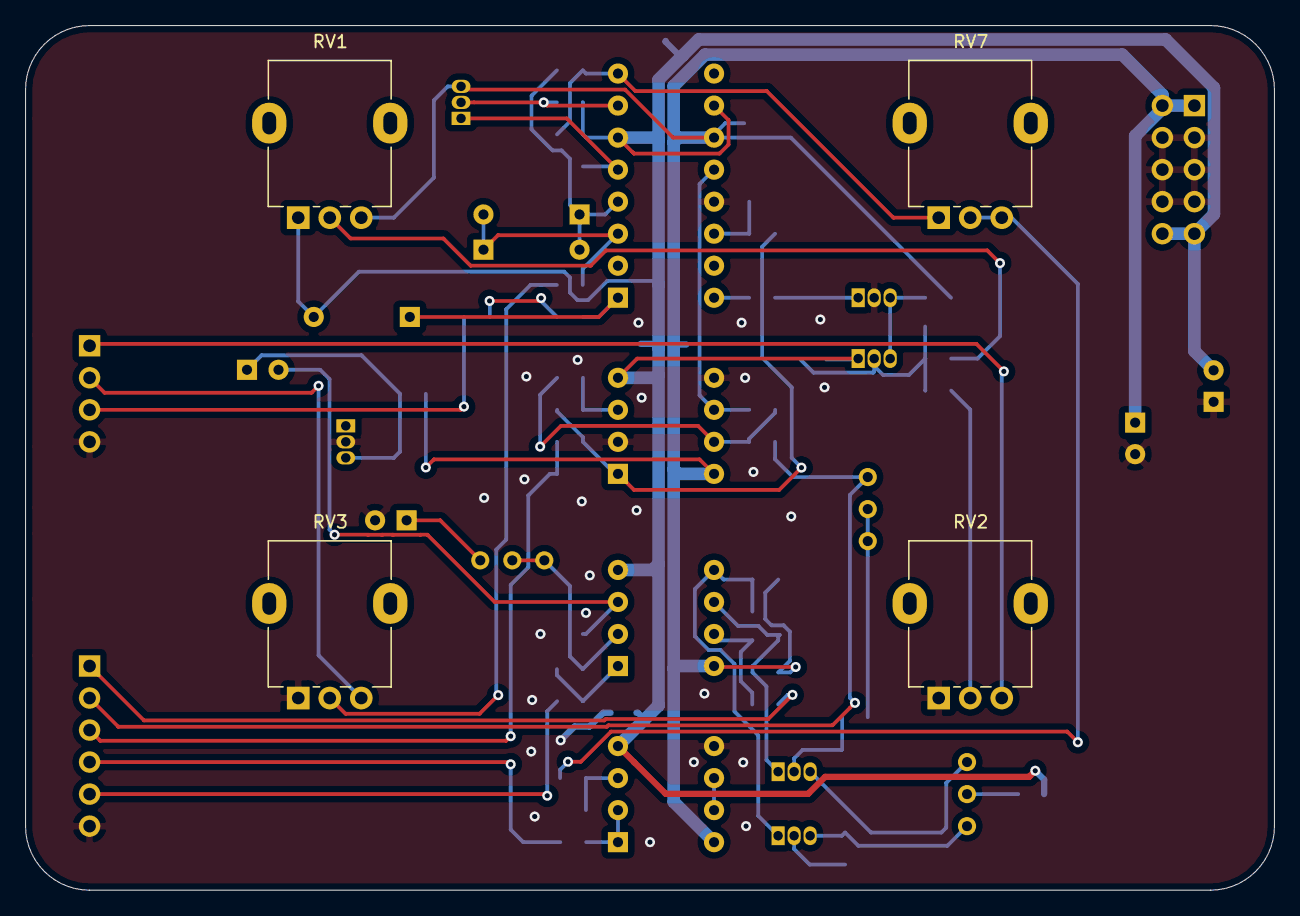
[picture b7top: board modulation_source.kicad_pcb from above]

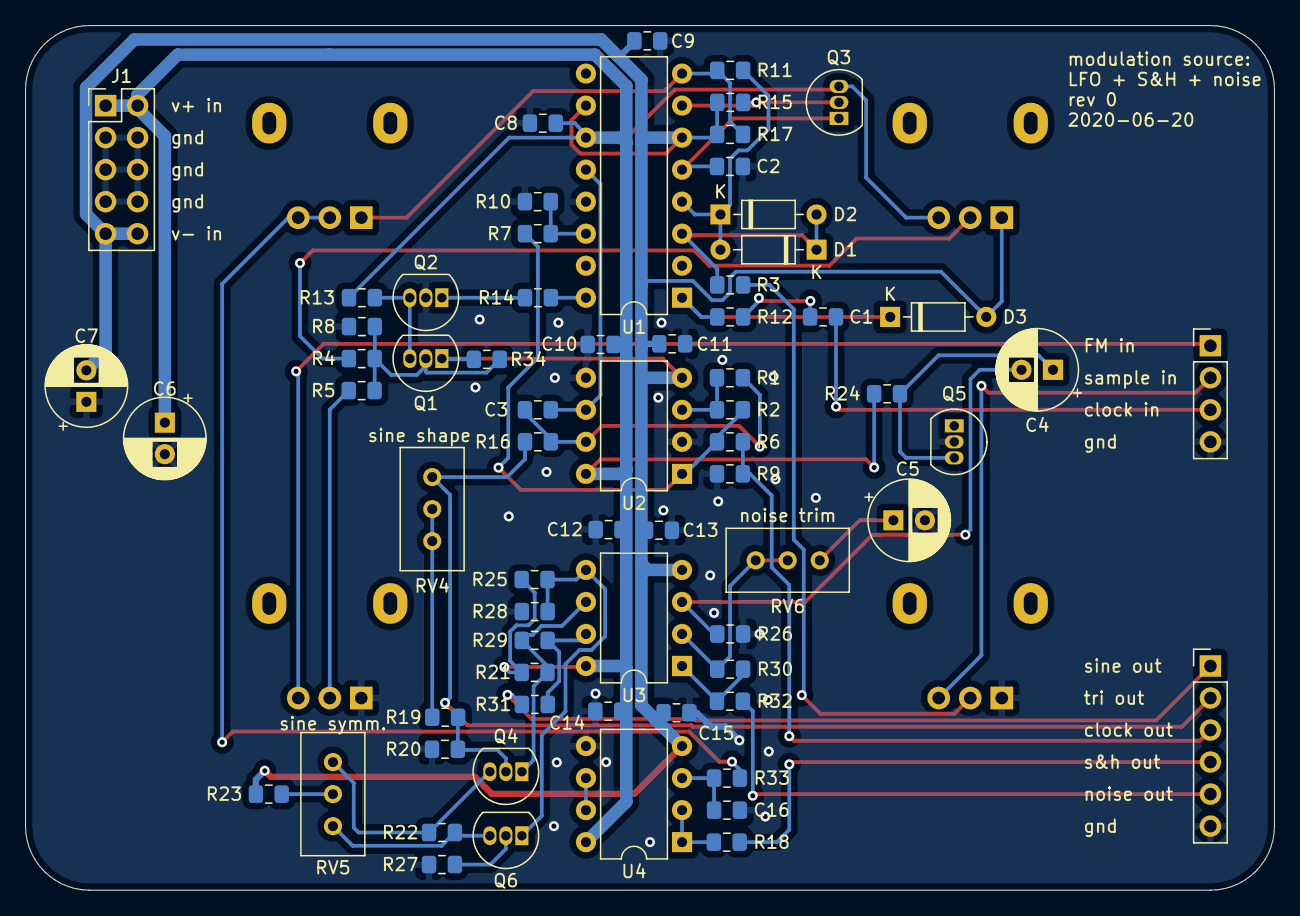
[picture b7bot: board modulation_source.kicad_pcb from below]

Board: 2 copper layers, 99.1 x 68.6 mm, 73 parts (69 on the bottom side), 48 nets.
